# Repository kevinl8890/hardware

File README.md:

# hardware
The base hardware designs for the buddyAssist system.

The hardware has been split into two seperate boards, the reciever and the transmitter.
Both can be used with one microcontroller.

VCC for the transmitter should not exceed 12V.
VCC for the reciever should not exceed 9V.

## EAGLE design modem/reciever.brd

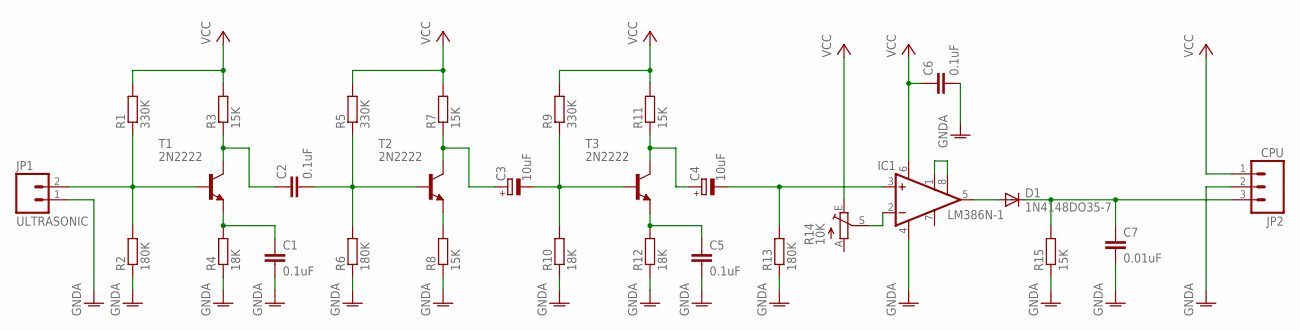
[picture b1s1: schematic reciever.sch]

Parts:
C1, C2, C5, C6: 0.1uF; C050-025X075
C3, C4: 10uF; E2,5-5
C7: 0.01uF; C050-025X075
D1: 1N4148DO35-7; DO35-7
IC1: LM386N-1; DIL08
JP1: ULTRASONIC; JST-2-PTH-VERT
JP2: CPU; JST-3-PTH-VERT
R1, R5, R9: 330K; 0204/7
R2, R6, R13: 180K; 0204/7
R3, R7, R8, R11, R15: 15K; 0204/7
R4, R10, R12: 18K; 0204/7
R14: 10K; B25P
T1, T2, T3: 2N2222; TO92-EBC

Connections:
GNDA: C1.2, C5.2, C6.2, C7.2, IC1.4 (GND), JP1.1, JP2.2, R2.1, R4.1, R6.1, R8.1, R10.1, R12.1, R13.1, R15.1
unnamed: JP1.2, R1.1, R2.2, T1.B
unnamed: C2.1, R3.1, T1.C
unnamed: C1.1, R4.2, T1.E
unnamed: R8.2, T2.E
unnamed: C2.2, R5.1, R6.2, T2.B
unnamed: C7.1, D1.C, JP2.3, R15.2
unnamed: C3.+, R7.1, T2.C
unnamed: C3.-, R9.1, R10.2, T3.B
unnamed: C5.1, R12.2, T3.E
unnamed: IC1.2 (-IN), R14.S
unnamed: C4.+, R11.1, T3.C
unnamed: C4.-, IC1.3 (+IN), R13.2
unnamed: IC1.1 (GAIN), IC1.8 (GAIN)
unnamed: D1.A, IC1.5 (OUT)
VCC: C6.1, IC1.6 (VS), JP2.1, R1.2, R3.2, R5.2, R7.2, R9.2, R11.2, R14.E

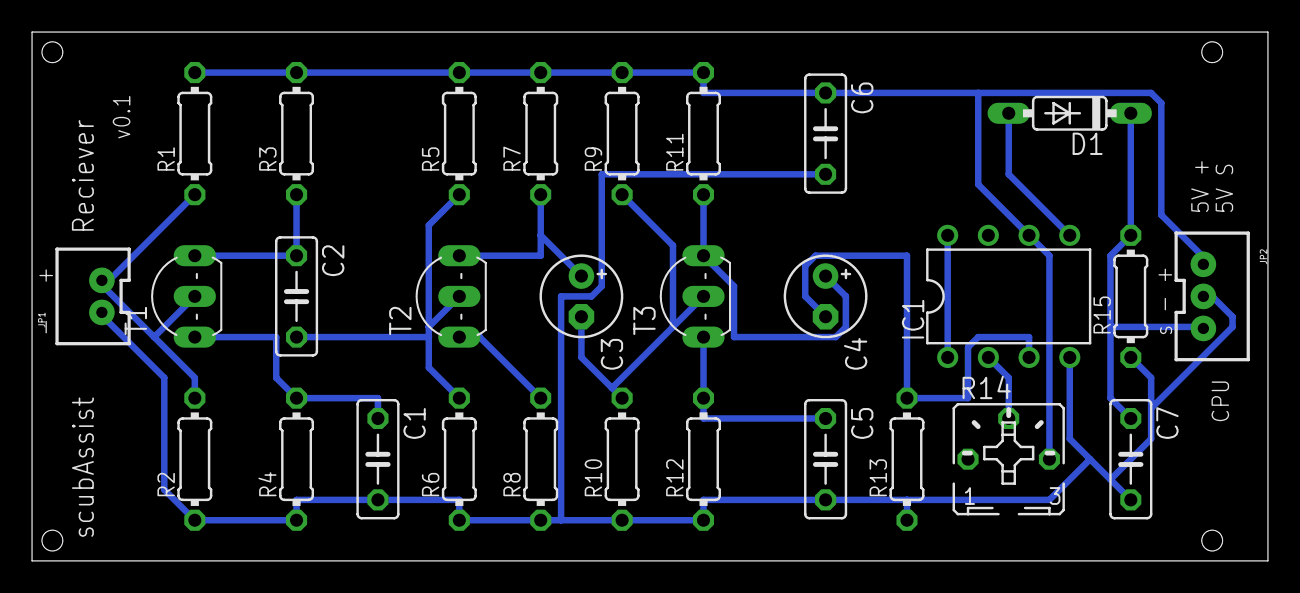
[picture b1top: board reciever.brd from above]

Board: 2 copper layers, 77.1 x 33.0 mm, 29 parts (0 on the bottom side), 16 nets.

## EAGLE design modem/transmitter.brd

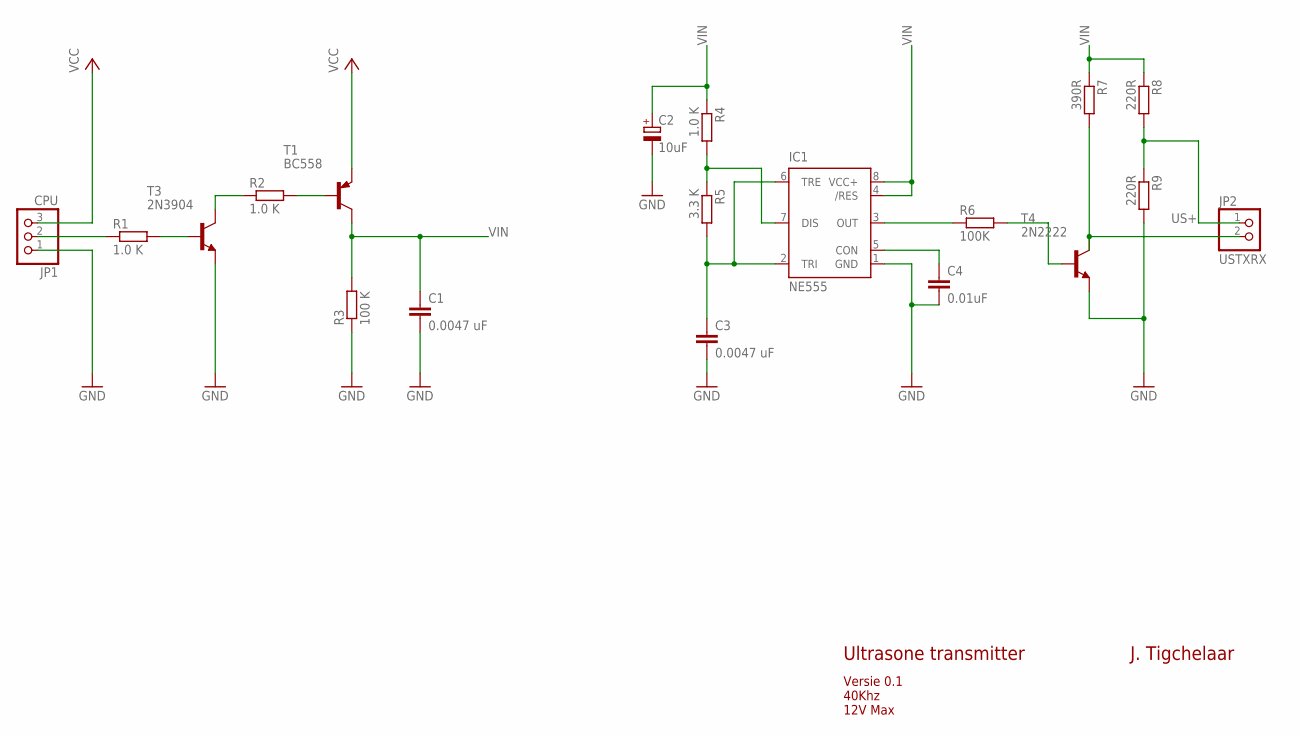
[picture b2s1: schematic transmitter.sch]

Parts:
C1, C3: 0.0047 uF; C025-025X050
C2: 10uF; E5-5
C4: 0.01uF; C025-025X050
IC1: NE555; DIL-08
JP1: CPU; 1X03
JP2: USTXRX; 1X02
R1, R2, R4: 1.0 K; 0207/10
R3: 100 K; 0207/10
R5: 3.3 K; 0207/10
R6: 100K; 0207/10
R7: 390R; 0207/10
R8, R9: 220R; 0207/10
T1: BC558; TO92-CBE
T3: 2N3904; TO92-EBC
T4: 2N2222; TO92-EBC

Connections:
GND: C1.2, C2.-, C3.2, C4.2, IC1.1 (GND), JP1.1, R3.1, R9.2, T3.E, T4.E
unnamed: C4.1, IC1.5 (CON)
unnamed: C3.1, IC1.2 (TRI), IC1.6 (TRE), R5.2
unnamed: IC1.7 (DIS), R4.2, R5.1
unnamed: R6.2, T4.B
unnamed: JP1.2, R1.1
unnamed: IC1.3 (OUT), R6.1
unnamed: JP2.2, R7.2, T4.C
unnamed: R1.2, T3.B
unnamed: R2.1, T3.C
unnamed: R2.2, T1.B
US+: JP2.1, R8.2, R9.1
VCC: JP1.3, T1.E
VIN: C1.1, C2.+, IC1.4 (/RES), IC1.8 (VCC+), R3.2, R4.1, R7.1, R8.1, T1.C

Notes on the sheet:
Ultrasone transmitter
Versie 0.1 40Khz 12V Max
J. Tigchelaar

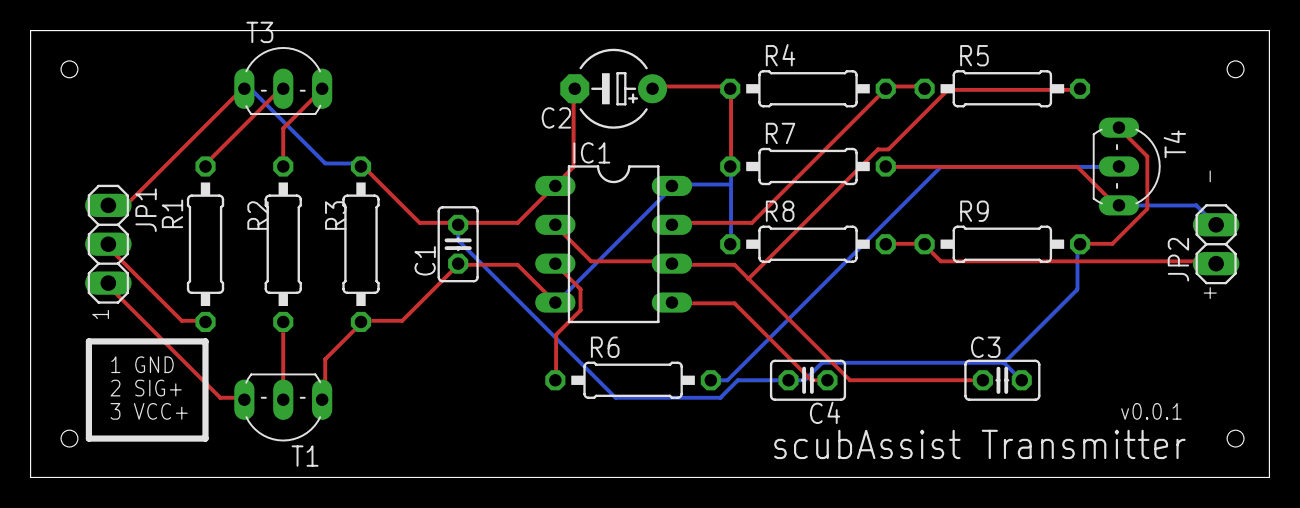
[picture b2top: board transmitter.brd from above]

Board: 2 copper layers, 81.0 x 29.2 mm, 19 parts (0 on the bottom side), 14 nets.

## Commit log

2016-06-09 Initial commit
    First version of receiver and transmitter boards. Omitted 1:10
    transformer in transmitter, needs board redesign and appropriate
    capacitor.

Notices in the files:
parts and their libraries:
SparkFun-Connectors: Licensing: Creative Commons ShareAlike 4.0 International - https://creativecommons.org/licenses/by-sa/4.0
